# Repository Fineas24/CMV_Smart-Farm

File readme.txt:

Fineas Opincă: sistemul de irigare partea software(raspberry pi cu modul de cameră, senzor de distanță, microcontroller raspberry pi pico cu modul de GPS), 
	       site-ul, 
	       sistemul de trimitere mesaje pe whatsapp.

Gabriel Barbu: asomatorul, proiectarea pieselor 3D în sketch up, sistemul de irigare partea hardware(placa de lemn, 3 pompe, 3 rezervoare)

Codul pentru conectarea la rețea, modulul GPS și pornirea pompelor a fost realizat în micropython.

Site-ul:
-backend - php
-frontend - html, css si js
-baza de date - mySQL

Codul pentru whatsapp(facere poze, senzor de distanță și trimitere pe whatsapp) a fost realizat în python, folosind node.js, npx. și mudslide.

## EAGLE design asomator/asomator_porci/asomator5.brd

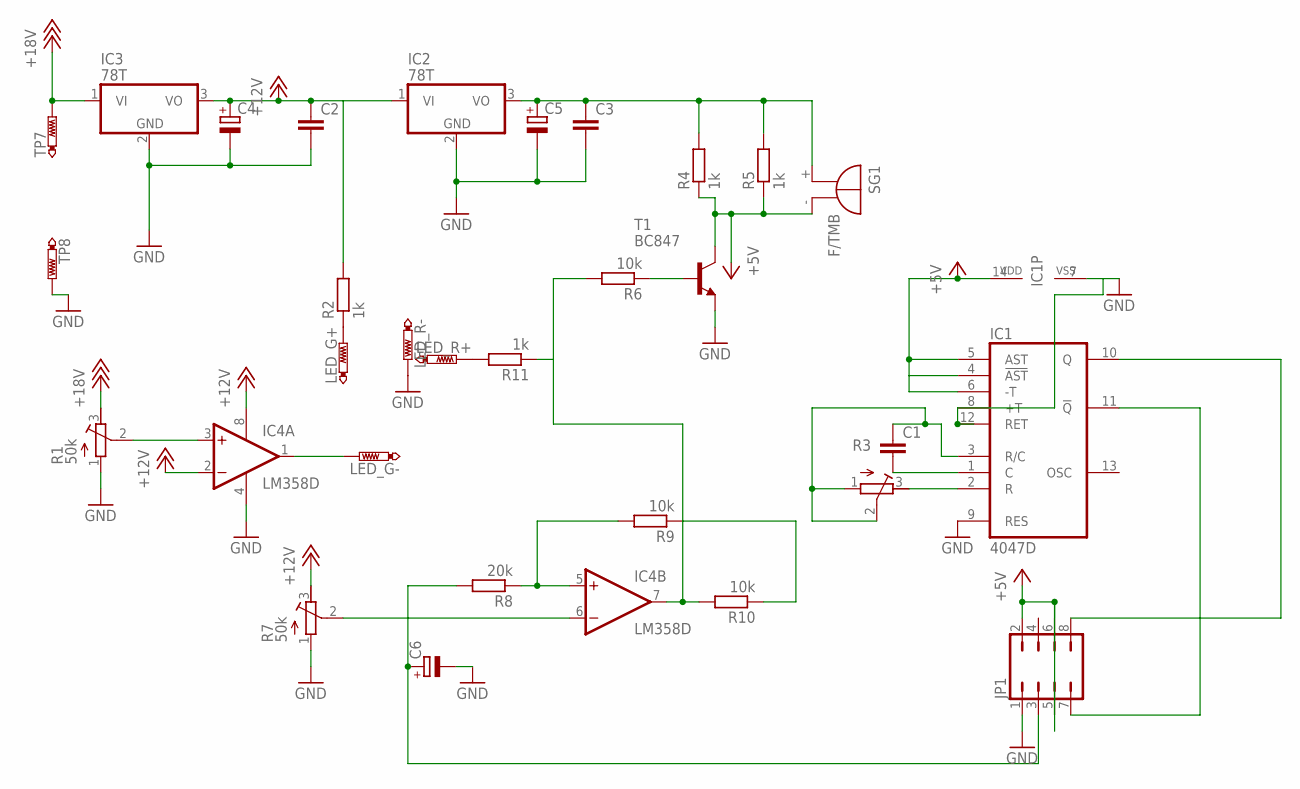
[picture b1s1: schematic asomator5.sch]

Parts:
C1, C2, C3: C-EUC1210; C1210
C4, C5, C6: CPOL-EUE2.5-7; E2,5-7
IC1: 4047D; SO14
IC2, IC3: 78T; TO220H
IC4: LM358D; SO08
JP1: JP4Q
LED_G+: PTR1PAD1-13Y; P1-13Y
LED_G-: PTR1PAD1-13Y; P1-13Y
LED_R+: PTR1PAD1-13Y; P1-13Y
LED_R-: PTR1PAD1-13Y; P1-13Y
R1, R7: 50k; RTRIM64W
R2, R4, R5, R11: 1k; R1206
R3: R-TRIMM4G/J; RTRIM4G/J
R6, R9, R10: 10k; R1206
R8: 20k; R1206
SG1: F/TMB
T1: BC847; SOT23
TP7, TP8: PTR1PAD1-13Y; P1-13Y

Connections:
+5V: IC1.4 (!AST), IC1.5 (AST), IC1.6 (-T), IC1.14 (VDD), JP1.2, JP1.5, JP1.6, R4.1, R5.1, SG1.-, T1.3 (C)
+12V: C2.1, C4.+, IC2.1 (VI), IC3.3 (VO), IC4.2 (-IN), IC4.8 (V+), R2.2, R7.3 (E)
+18V: IC3.1 (VI), R1.3 (E), TP7.TP
GND: C2.2, C3.2, C4.-, C5.-, C6.-, IC1.7 (VSS), IC1.8 (+T), IC1.9 (RES), IC1.12 (RET), IC2.2 (GND), IC3.2 (GND), IC4.4 (V-), JP1.1, LED_R-.TP, R1.1 (A), R7.1 (A), T1.2 (E), TP8.TP
unnamed: LED_G+.TP, R2.1
unnamed: LED_R+.TP, R11.2
unnamed: IC4.1 (OUT), LED_G-.TP
unnamed: IC4.3 (+IN), R1.2 (S)
unnamed: IC4.7 (OUT), R6.2, R10.2, R11.1
unnamed: IC1.2 (R), R3.3 (E)
unnamed: C1.2, IC1.1 (C)
unnamed: C1.1, IC1.3 (R/C), R3.1 (A), R3.2 (S)
unnamed: C3.1, C5.+, IC2.3 (VO), R4.2, R5.2, SG1.+
unnamed: IC1.10 (Q), JP1.8
unnamed: IC4.5 (+IN), R8.1, R9.2
unnamed: R9.1, R10.1
unnamed: IC4.6 (-IN), R7.2 (S)
unnamed: IC1.11 (!Q), JP1.7
unnamed: C6.+, JP1.3, R8.2
unnamed: R6.1, T1.1 (B)

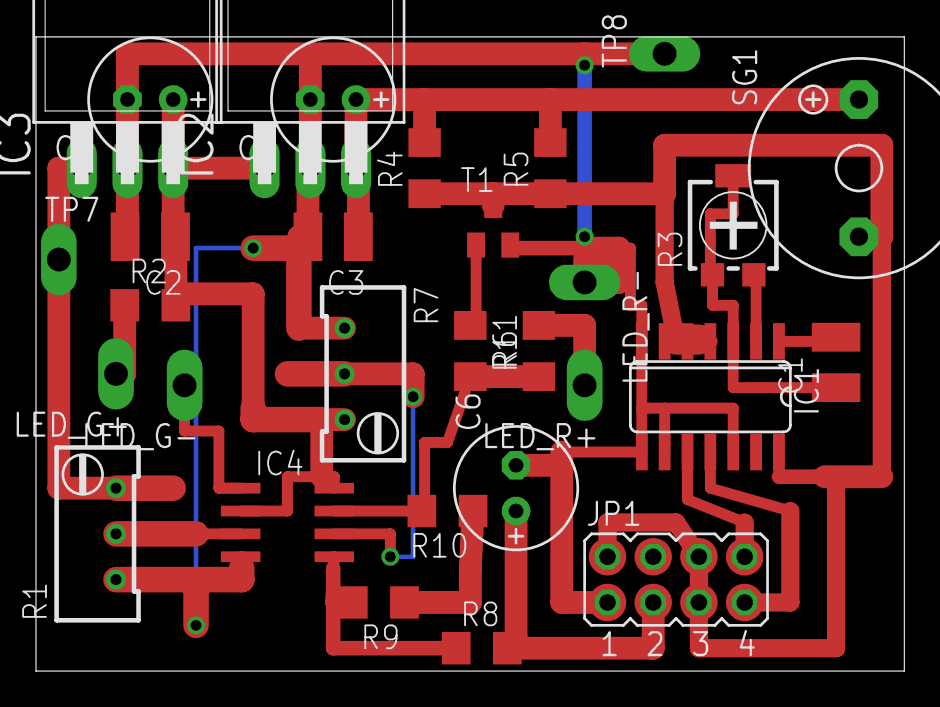
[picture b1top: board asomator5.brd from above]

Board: 3 copper layers, 48.2 x 35.2 mm, 30 parts (0 on the bottom side), 20 nets.

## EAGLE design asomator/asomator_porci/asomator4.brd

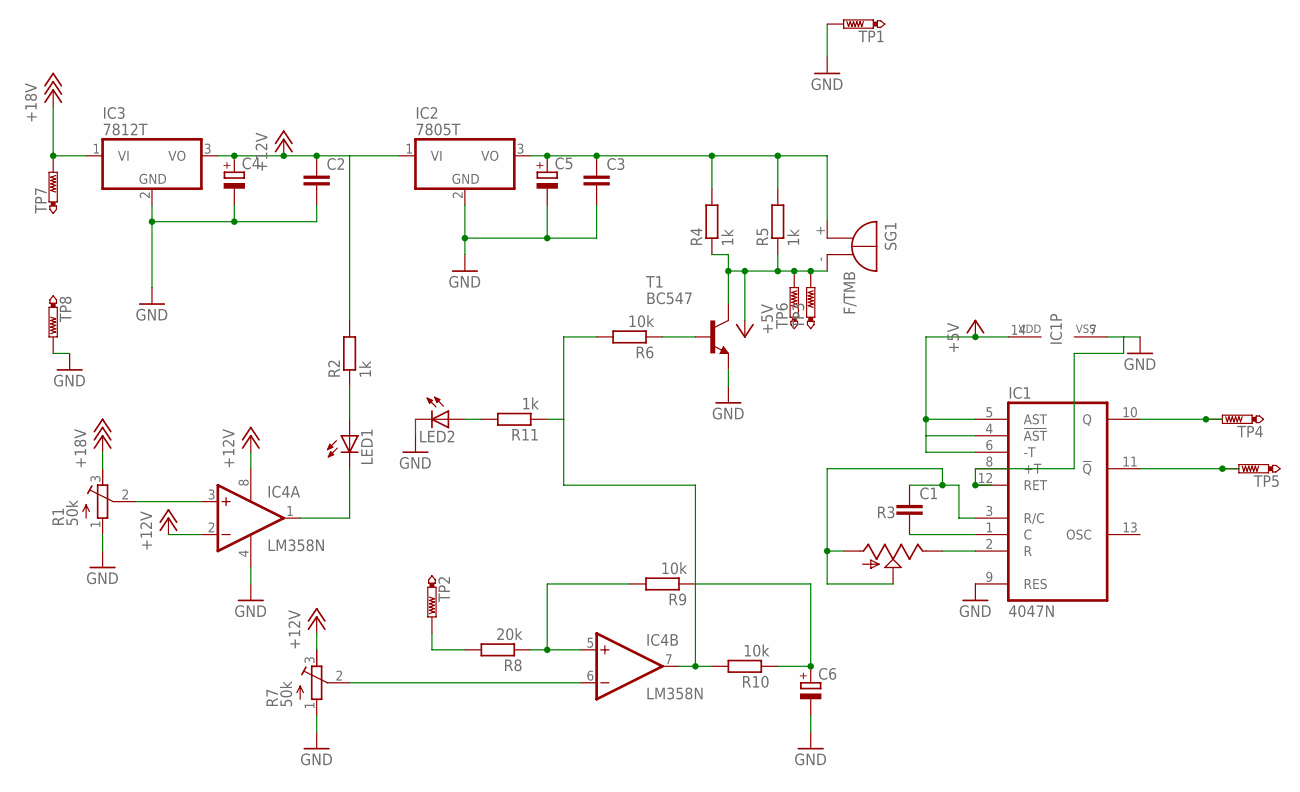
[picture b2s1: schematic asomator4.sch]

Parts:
C1, C2, C3: C-EU025-030X050; C025-030X050
C4, C5, C6: CPOL-EUE2.5-6; E2,5-6
IC1: 4047N; DIL14
IC2: 7805T; TO220H
IC3: 7812T; TO220H
IC4: LM358N; DIL08
LED1, LED2: LED5MM
R1, R7: 50k; RTRIM64W
R2, R4, R5, R11: 1k; 0207/10
R3: TRIM_US-CA9V; CA9V
R6, R9, R10: 10k; 0207/10
R8: 20k; 0207/10
SG1: F/TMB
T1: BC547; TO92
TP1, TP2, TP3, TP4, TP5, TP6, TP7, TP8: PTR1PAD1-13Y; P1-13Y

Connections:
+5V: IC1.4 (!AST), IC1.5 (AST), IC1.6 (-T), IC1.14 (VDD), R4.1, R5.1, SG1.-, T1.3 (C), TP3.TP, TP6.TP
+12V: C2.1, C4.+, IC2.1 (VI), IC3.3 (VO), IC4.2 (-IN), IC4.8 (V+), R2.2, R7.3 (E)
+18V: IC3.1 (VI), R1.3 (E), TP7.TP
GND: C2.2, C3.2, C4.-, C5.-, C6.-, IC1.7 (VSS), IC1.8 (+T), IC1.9 (RES), IC1.12 (RET), IC2.2 (GND), IC3.2 (GND), IC4.4 (V-), LED2.K (C), R1.1 (A), R7.1 (A), T1.1 (E), TP1.TP, TP8.TP
unnamed: IC1.10 (Q), TP4.TP
unnamed: LED1.A, R2.1
unnamed: IC1.11 (!Q), TP5.TP
unnamed: IC4.1 (OUT), LED1.K (C)
unnamed: IC4.3 (+IN), R1.2 (S)
unnamed: IC4.7 (OUT), R6.2, R10.2, R11.1
unnamed: IC1.2 (R), R3.E
unnamed: C1.2, IC1.1 (C)
unnamed: C1.1, IC1.3 (R/C), R3.A, R3.S
unnamed: C3.1, C5.+, IC2.3 (VO), R4.2, R5.2, SG1.+
unnamed: LED2.A, R11.2
unnamed: R8.2, TP2.TP
unnamed: IC4.5 (+IN), R8.1, R9.2
unnamed: C6.+, R9.1, R10.1
unnamed: IC4.6 (-IN), R7.2 (S)
unnamed: R6.1, T1.2 (B)

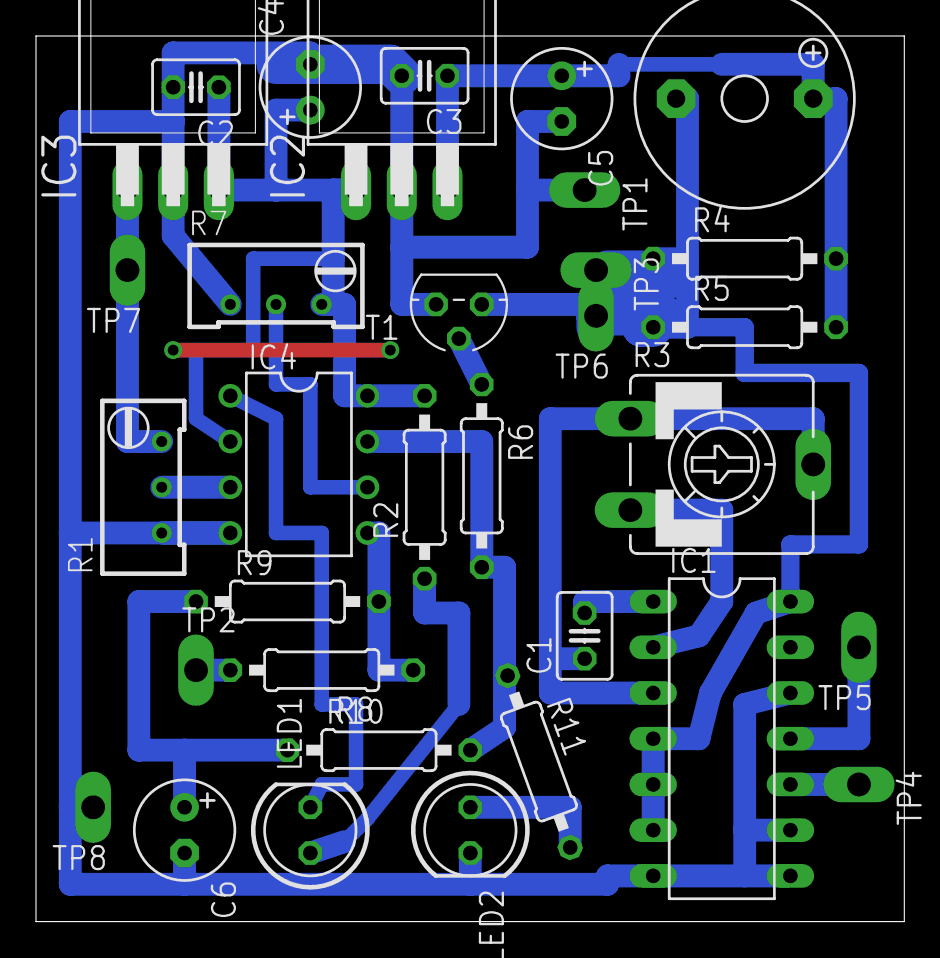
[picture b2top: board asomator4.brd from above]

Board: 3 copper layers, 48.2 x 49.2 mm, 33 parts (0 on the bottom side), 20 nets.

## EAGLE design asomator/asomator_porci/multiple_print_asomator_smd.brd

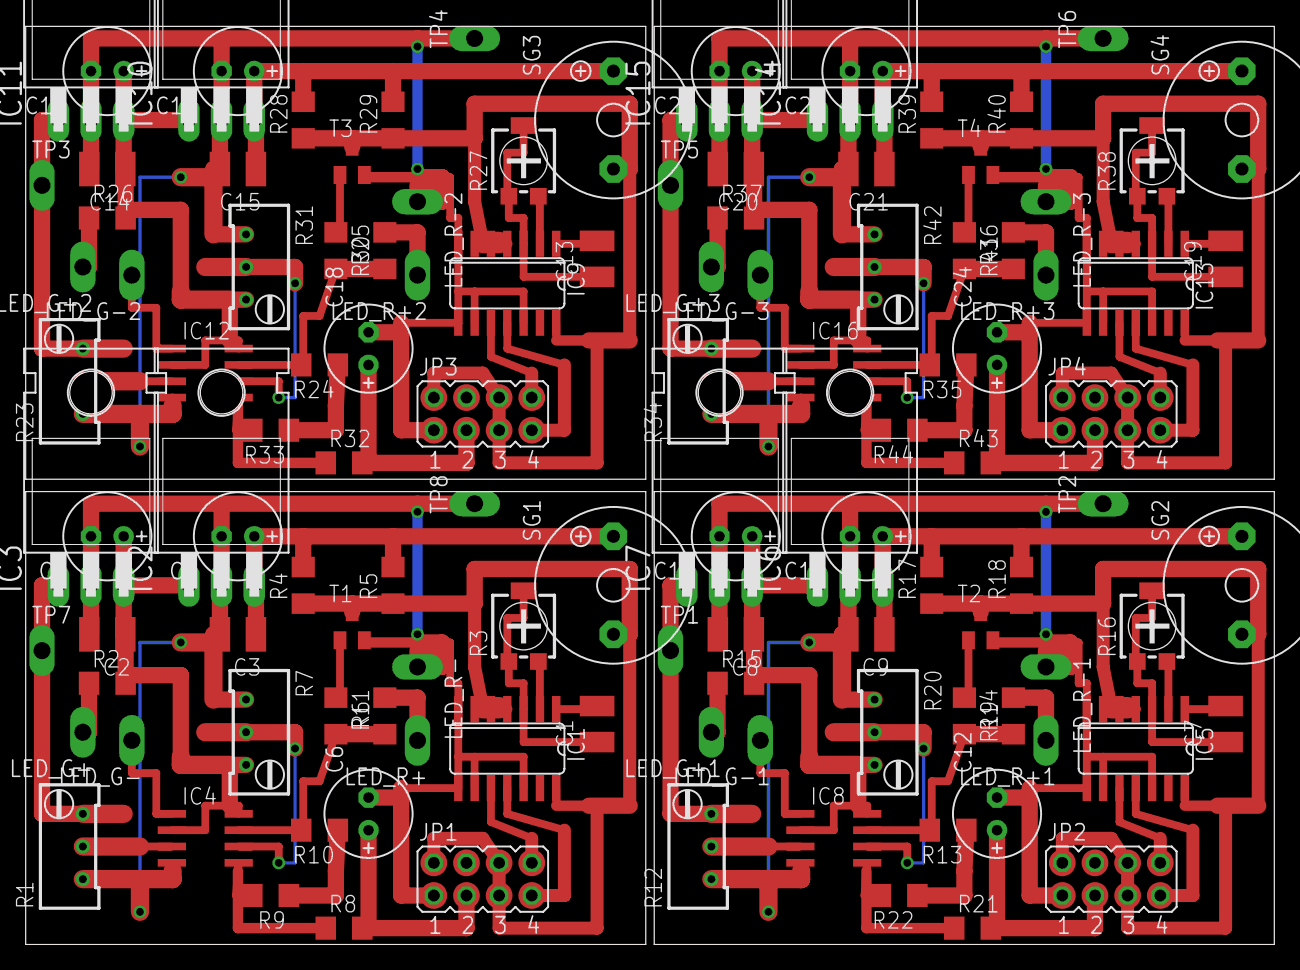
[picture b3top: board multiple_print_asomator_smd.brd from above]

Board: 3 copper layers, 97.1 x 71.4 mm, 120 parts (0 on the bottom side), 80 nets.

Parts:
C1, C2, C3, C7, C8, C9, C13, C14, C15, C19, C20, C21: C1210
C4, C5, C6, C10, C11, C12, C16, C17, C18, C22, C23, C24: E2,5-7
IC1, IC5, IC9, IC13: 4047D; SO14
IC2, IC3, IC6, IC7, IC10, IC11, IC14, IC15: 78T; TO220H
IC4, IC8, IC12, IC16: LM358D; SO08
JP1, JP2, JP3, JP4: JP4Q
LED_G+, LED_G+1, LED_G+2, LED_G+3: PTR1PAD1-13Y; P1-13Y
LED_G-, LED_G-1, LED_G-2, LED_G-3: PTR1PAD1-13Y; P1-13Y
LED_R+, LED_R+1, LED_R+2, LED_R+3: PTR1PAD1-13Y; P1-13Y
LED_R-, LED_R-1, LED_R-2, LED_R-3: PTR1PAD1-13Y; P1-13Y
R1, R7, R12, R20, R23, R31, R34, R42: 50k; RTRIM64W
R2, R4, R5, R11, R14, R15, R17, R18, R25, R26, R28, R29, R36, R37, R39, R40: 1k; R1206
R3, R16, R27, R38: RTRIM4G/J
R6, R9, R10, R13, R19, R22, R24, R30, R33, R35, R41, R44: 10k; R1206
R8, R21, R32, R43: 20k; R1206
SG1, SG2, SG3, SG4: F/TMB
T1, T2, T3, T4: BC847; SOT23
TP1, TP2, TP3, TP4, TP5, TP6, TP7, TP8: PTR1PAD1-13Y; P1-13Y

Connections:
+5V: IC1.4, IC1.5, IC1.6, IC1.14, JP1.2, JP1.5, JP1.6, R4.1, R5.1, SG1.-, T1.3
+5V1: IC5.4, IC5.5, IC5.6, IC5.14, JP2.2, JP2.5, JP2.6, R17.1, R18.1, SG2.-, T2.3
+5V2: IC9.4, IC9.5, IC9.6, IC9.14, JP3.2, JP3.5, JP3.6, R28.1, R29.1, SG3.-, T3.3
+5V3: IC13.4, IC13.5, IC13.6, IC13.14, JP4.2, JP4.5, JP4.6, R39.1, R40.1, SG4.-, T4.3
+12V: C2.1, C4.+, IC2.1, IC3.3, IC4.2, IC4.8, R2.2, R7.3
+12V1: C8.1, C10.+, IC6.1, IC7.3, IC8.2, IC8.8, R15.2, R20.3
+12V2: C14.1, C16.+, IC10.1, IC11.3, IC12.2, IC12.8, R26.2, R31.3
+12V3: C20.1, C22.+, IC14.1, IC15.3, IC16.2, IC16.8, R37.2, R42.3
+18V: IC3.1, R1.3, TP7.TP
+18V1: IC7.1, R12.3, TP1.TP
+18V2: IC11.1, R23.3, TP3.TP
+18V3: IC15.1, R34.3, TP5.TP
GND: C2.2, C3.2, C4.-, C5.-, C6.-, IC1.7, IC1.8, IC1.9, IC1.12, IC2.2, IC3.2, IC4.4, JP1.1, LED_R-.TP, R1.1, R7.1, T1.2, TP8.TP
GND1: C8.2, C9.2, C10.-, C11.-, C12.-, IC5.7, IC5.8, IC5.9, IC5.12, IC6.2, IC7.2, IC8.4, JP2.1, LED_R-1.TP, R12.1, R20.1, T2.2, TP2.TP
GND2: C14.2, C15.2, C16.-, C17.-, C18.-, IC9.7, IC9.8, IC9.9, IC9.12, IC10.2, IC11.2, IC12.4, JP3.1, LED_R-2.TP, R23.1, R31.1, T3.2, TP4.TP
GND3: C20.2, C21.2, C22.-, C23.-, C24.-, IC13.7, IC13.8, IC13.9, IC13.12, IC14.2, IC15.2, IC16.4, JP4.1, LED_R-3.TP, R34.1, R42.1, T4.2, TP6.TP
unnamed: LED_G+.TP, R2.1
unnamed: LED_R+.TP, R11.2
unnamed: IC4.1, LED_G-.TP
unnamed: IC4.3, R1.2
unnamed: IC4.7, R6.2, R10.2, R11.1
unnamed: IC1.2, R3.3
unnamed: C1.2, IC1.1
unnamed: C1.1, IC1.3, R3.1, R3.2
unnamed: C3.1, C5.+, IC2.3, R4.2, R5.2, SG1.+
unnamed: IC1.10, JP1.8
unnamed: IC4.5, R8.1, R9.2
unnamed: R9.1, R10.1
unnamed: IC4.6, R7.2
unnamed: IC1.11, JP1.7
unnamed: C6.+, JP1.3, R8.2
unnamed: R6.1, T1.1
unnamed: IC5.2, R16.3
unnamed: C7.2, IC5.1
unnamed: C7.1, IC5.3, R16.1, R16.2
unnamed: IC8.1, LED_G-1.TP
unnamed: IC8.3, R12.2
unnamed: C9.1, C11.+, IC6.3, R17.2, R18.2, SG2.+
unnamed: IC8.6, R20.2
unnamed: IC8.5, R21.1, R22.2
unnamed: R13.1, R22.1
unnamed: R19.1, T2.1
unnamed: IC8.7, R13.2, R14.1, R19.2
unnamed: IC5.10, JP2.8
unnamed: IC5.11, JP2.7
unnamed: C12.+, JP2.3, R21.2
unnamed: LED_G+1.TP, R15.1
unnamed: LED_R+1.TP, R14.2
unnamed: IC9.2, R27.3
unnamed: C13.2, IC9.1
unnamed: C13.1, IC9.3, R27.1, R27.2
unnamed: IC12.1, LED_G-2.TP
unnamed: IC12.3, R23.2
unnamed: C15.1, C17.+, IC10.3, R28.2, R29.2, SG3.+
unnamed: IC12.6, R31.2
unnamed: IC12.5, R32.1, R33.2
unnamed: R24.1, R33.1
unnamed: R30.1, T3.1
unnamed: IC12.7, R24.2, R25.1, R30.2
unnamed: IC9.10, JP3.8
unnamed: IC9.11, JP3.7
unnamed: C18.+, JP3.3, R32.2
unnamed: LED_G+2.TP, R26.1
unnamed: LED_R+2.TP, R25.2
unnamed: IC13.2, R38.3
unnamed: C19.2, IC13.1
unnamed: C19.1, IC13.3, R38.1, R38.2
unnamed: IC16.1, LED_G-3.TP
unnamed: IC16.3, R34.2
unnamed: C21.1, C23.+, IC14.3, R39.2, R40.2, SG4.+
unnamed: IC16.6, R42.2
unnamed: IC16.5, R43.1, R44.2
unnamed: R35.1, R44.1
unnamed: R41.1, T4.1
unnamed: IC16.7, R35.2, R36.1, R41.2
unnamed: IC13.10, JP4.8
unnamed: IC13.11, JP4.7
unnamed: C24.+, JP4.3, R43.2
unnamed: LED_G+3.TP, R37.1
unnamed: LED_R+3.TP, R36.2

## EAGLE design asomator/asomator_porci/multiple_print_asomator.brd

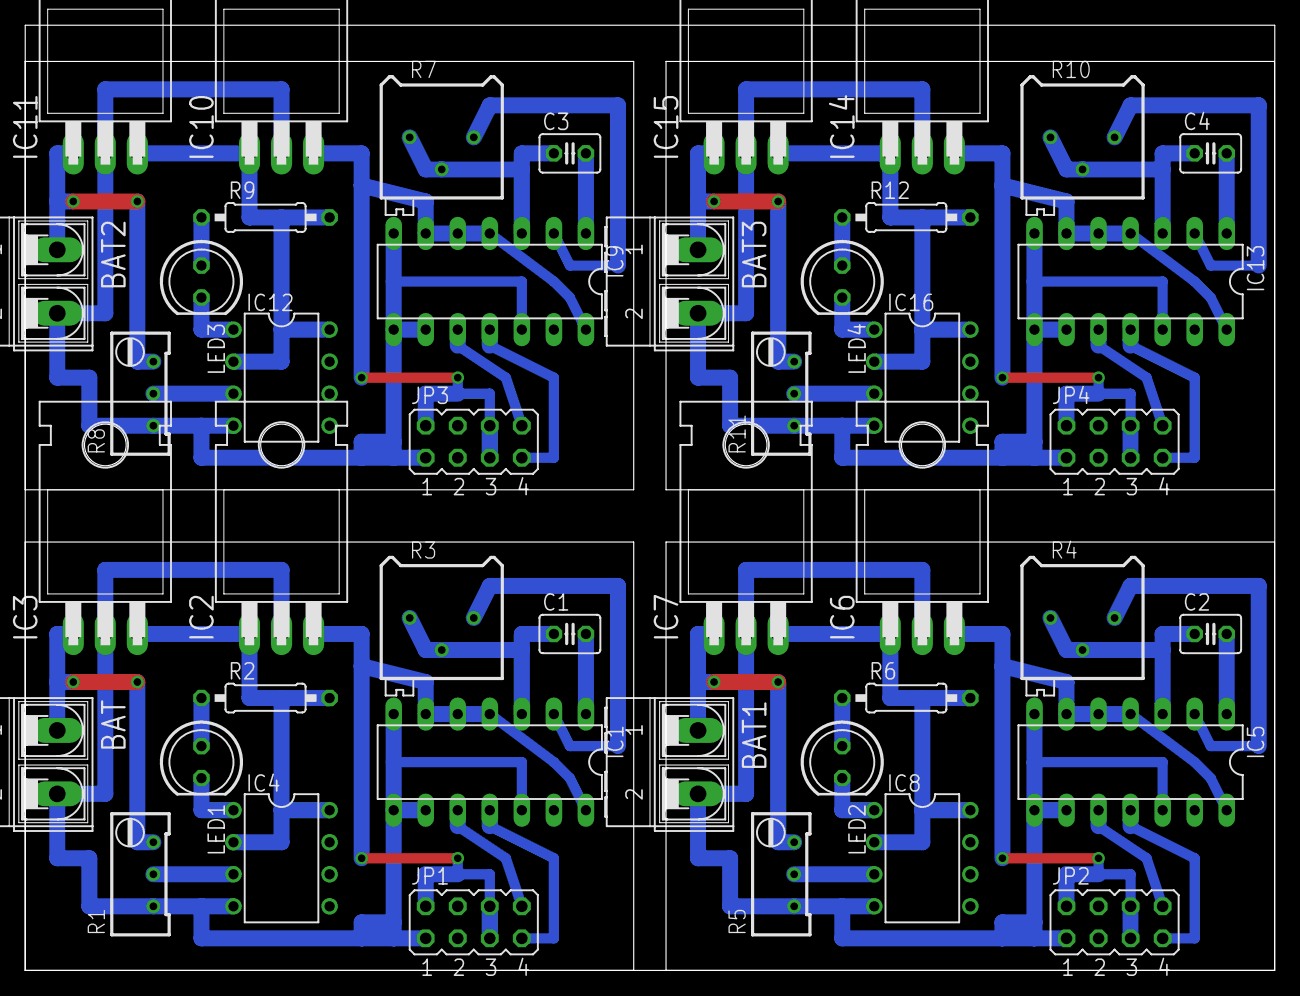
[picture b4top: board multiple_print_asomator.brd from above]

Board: 3 copper layers, 99.1 x 74.9 mm, 44 parts (0 on the bottom side), 48 nets.

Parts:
BAT, BAT1, BAT2, BAT3: AK500/2-H
C1, C2, C3, C4: C025-030X050
IC1, IC5, IC9, IC13: 4047N; DIL14
IC2, IC6, IC10, IC14: 7805T; TO220H
IC3, IC7, IC11, IC15: 7812T; TO220H
IC4, IC8, IC12, IC16: LM358N; DIL08
JP1, JP2, JP3, JP4: JP4Q
LED1, LED2, LED3, LED4: LED5MM
R1, R5, R8, R11: RTRIM64W
R2, R6, R9, R12: 0207/10
R3, R4, R7, R10: RTRIM64P

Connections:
+5V: IC1.4, IC1.5, IC1.6, IC1.14, IC2.3, JP1.2, JP1.5, JP1.6
+5V1: IC5.4, IC5.5, IC5.6, IC5.14, IC6.3, JP2.2, JP2.5, JP2.6
+5V2: IC9.4, IC9.5, IC9.6, IC9.14, IC10.3, JP3.2, JP3.5, JP3.6
+5V3: IC13.4, IC13.5, IC13.6, IC13.14, IC14.3, JP4.2, JP4.5, JP4.6
+12V: IC2.1, IC3.3, IC4.2, IC4.8, R2.2
+12V1: IC6.1, IC7.3, IC8.2, IC8.8, R6.2
+12V2: IC10.1, IC11.3, IC12.2, IC12.8, R9.2
+12V3: IC14.1, IC15.3, IC16.2, IC16.8, R12.2
+18V: BAT.1, IC3.1, R1.3
+18V1: BAT1.1, IC7.1, R5.3
+18V2: BAT2.1, IC11.1, R8.3
+18V3: BAT3.1, IC15.1, R11.3
GND: BAT.2, IC1.7, IC1.8, IC1.9, IC1.12, IC2.2, IC3.2, IC4.4, JP1.1, R1.1
GND1: BAT1.2, IC5.7, IC5.8, IC5.9, IC5.12, IC6.2, IC7.2, IC8.4, JP2.1, R5.1
GND2: BAT2.2, IC9.7, IC9.8, IC9.9, IC9.12, IC10.2, IC11.2, IC12.4, JP3.1, R8.1
GND3: BAT3.2, IC13.7, IC13.8, IC13.9, IC13.12, IC14.2, IC15.2, IC16.4, JP4.1, R11.1
unnamed: IC1.10, JP1.8
unnamed: LED1.A, R2.1
unnamed: IC1.11, JP1.7
unnamed: IC4.1, LED1.K
unnamed: IC4.3, R1.2
unnamed: IC5.10, JP2.8
unnamed: IC1.2, R3.3
unnamed: C1.2, IC1.1
unnamed: C1.1, IC1.3, R3.1, R3.2
unnamed: IC5.11, JP2.7
unnamed: IC5.2, R4.3
unnamed: C2.2, IC5.1
unnamed: C2.1, IC5.3, R4.1, R4.2
unnamed: LED2.A, R6.1
unnamed: IC8.1, LED2.K
unnamed: IC8.3, R5.2
unnamed: IC9.10, JP3.8
unnamed: IC9.11, JP3.7
unnamed: IC9.2, R7.3
unnamed: C3.2, IC9.1
unnamed: C3.1, IC9.3, R7.1, R7.2
unnamed: LED3.A, R9.1
unnamed: IC12.1, LED3.K
unnamed: IC12.3, R8.2
unnamed: IC13.10, JP4.8
unnamed: IC13.11, JP4.7
unnamed: IC13.2, R10.3
unnamed: C4.2, IC13.1
unnamed: C4.1, IC13.3, R10.1, R10.2
unnamed: LED4.A, R12.1
unnamed: IC16.1, LED4.K
unnamed: IC16.3, R11.2
